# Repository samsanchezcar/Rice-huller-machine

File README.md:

<div align="center">

# DAMSPI-150
## Descascaradora de Arroz Modular Semiautomática con Pesaje Integrado

**Proyecto Aplicado de Ingeniería — 2017275 | 1er Semestre 2026**
**Universidad Nacional de Colombia · Facultad de Ingeniería · Grupo B**

</div>

---

## Tabla de Contenido

1. [Resumen Ejecutivo](#1-resumen-ejecutivo)
2. [Equipo de Trabajo](#2-equipo-de-trabajo)
3. [Estructura del Repositorio](#3-estructura-del-repositorio)
4. [Arquitectura del Sistema](#4-arquitectura-del-sistema)
5. [Guía de Fase del Proyecto](#5-guía-de-fase-del-proyecto)
6. [Proveedores Clave](#6-proveedores-clave)
7. [Instrucciones de Uso](#7-instrucciones-de-uso)
8. [Estado de Componentes](#8-estado-de-componentes)
9. [Pendientes por Fase](#9-pendientes-por-fase)
10. [Normas y Convenciones del Repositorio](#10-normas-y-convenciones-del-repositorio)

---

## 1. Resumen Ejecutivo

El **DAMSPI-150** es un equipo semiautomático para el descascarillado de arroz paddy (*Oryza sativa*) diseñado para operar en campo, sin acceso a red eléctrica, con capacidad de **150 kg/h**. Surge de la necesidad de los pequeños y medianos productores de arroz de la región de Neiva (Huila) de reducir su dependencia de los molinos industriales y aumentar el valor agregado de su producto en origen.

El sistema está organizado en **4 módulos desmontables** con peso máximo de 25 kg cada uno, permitiendo su transporte y montaje por dos o tres personas sin herramientas especializadas. Incorpora un **sistema de control automático de pesaje** que detiene el proceso al alcanzar el peso de un bulto objetivo (10, 25 o 50 kg), accionando el embrague electromagnético y la compuerta de la tolva.

| Parámetro | Valor |
|-----------|-------|
| Nombre del sistema | DAMSPI-150 |
| Solicitante | Diego Alexander Castro Neira — Diego Castro Industria y Construcción S.A.S. |
| Capacidad objetivo | 150 kg/h de arroz paddy (humedad 18–22%) |
| Motor | Gasolina 6.5 HP / 3600 RPM (ya adquirido) |
| Módulos | 4 módulos desmontables (Potencia, Descascarillado, Control/Pesaje, Chasis) |
| Peso máx. por módulo | ≤ 25 kg |
| Presupuesto total | $7.000.000 COP (aportado por solicitante) |
| Presupuesto estimado | ~$5.980.000 COP (margen de ~$1.020.000) |
| Microcontrolador | PIC18F4550 |
| Interfaz de usuario | LCD 20×4 I2C + Teclado matricial 4×4 |
| Embrague | Electromagnético DC 24V — DLD6-05 tipo A |
| Eficiencia descascarillado | ≥ 85% en primera pasada |
| Precisión pesaje | ±100 g |
| Tiempo de ensamble | ≤ 60 minutos |
| Piezas estructurales | Manufactura aditiva FDM (PETG / PLA+) con optimización topológica previa |
| Semestre | 1er Semestre 2026 (14 semanas: 3 Feb – 30 May 2026) |

---

## 2. Equipo de Trabajo

| Nombre | Código | Área Principal | Responsabilidades Clave |
|--------|--------|---------------|------------------------|
| **Nicolás Herreño Fuentes** | — | Diseño Mecánico (Líder) | Cálculos de transmisión, memorias de cálculo, CAD Onshape, planos de fabricación |
| **Sebastián D. Millan B.** | — | Diseño Mecánico | Cálculos elementos de máquinas, CAD, diseño eje secundario |
| **Andrés G. Pinilla M.** | — | Manufactura y CAD | Talleres externos, Onshape, optimización topológica + FDM |
| **Samuel D. Sánchez C.** | — | Electrónica / Control / **Gestión** | Firmware PIC18F4550, sistema de pesaje, **gestión de proveedores, cotizaciones, BOM, compras**, finanzas |
| **Gabriel E. Bojacá M.** | — | Electrónica / Financiero | Circuito electrónico, PCB, interfaz LCD-teclado, gestión presupuesto |
| **Santiago Ávila C.** | — | Eléctrico / Potencia | Alternador, carga batería, cableado potencia, sistema eléctrico Módulo 1 |

> **Nota de gestión**: Samuel es el responsable único de toda la coordinación con proveedores: contacto inicial, solicitud de cotizaciones, seguimiento de pedidos, recepción de componentes y registro en el BOM. Toda compra debe quedar registrada antes de ejecutarse.

---

## 3. Estructura del Repositorio

```
DAMSPI-150/
│
├── README.md                          ← Este archivo — guía maestra del proyecto
│
├── 01_Informe/                        ← Informes de avance (Partes I, II y III)
│   ├── Informe_Avance_Parte_I_Descascaradora.docx   ← Entrega S4 (completada)
│   ├── Informe_Parte_II_Diseño_Detallado.docx        ← Entrega S8 (en progreso)
│   ├── Informe_Parte_III_Final.docx                  ← Entrega S14 (pendiente)
│   ├── boceto_arquitectura_modular.png
│   ├── sistema_potencia_electrica.svg
│   └── Diagramas_bloques.pdf
│
├── 02_Actas/                          ← Actas semanales y documentos legales
│   ├── Acuerdo_Solicitante.pdf        ← AS firmado
│   ├── contrato_social.pdf            ← CS firmado
│   ├── Acta_S01.pdf
│   ├── Acta_S02.pdf
│   ├── Acta_S03.pdf
│   └── Acta_SColchon.pdf
│
├── 03_Cronograma_GANTT/               ← Planificación y seguimiento
│   ├── GANTT_Descascaradora_v2.xlsx   ← GANTT original (referencia)
│   └── GANTT-PAI1B.pdf
│
├── 04_BOM/                            ← Lista de materiales
│   └── BOM_Descascaradora_v1.xlsx     ← BOM con 34 ítems (~$5.98M COP)
│
├── 05_CAD_Planos/                     ← Modelos 3D y planos de fabricación
│   ├── Onshape_Link.md                ← Enlace al modelo Onshape compartido
│   └── (exportar aquí planos PDF/DWG al finalizar cada módulo)
│
├── 06_Estado_del_Arte_Referencias/    ← Literatura técnica y normativa
│   ├── Baker_Tribologia_Molineria_Arroz.pdf
│   ├── Design_Fabrication_Rice_Hulling.pdf
│   ├── Manual_Tecnico_Descascaradora_Referencia.pdf
│   ├── Referencia_Adicional_Procesamiento_Arroz.pdf
│   └── rm05.pdf
│
├── 07_Bitacoras/                      ← Bitácoras semanales individuales
│   ├── Bitacora_Nicolas.md
│   ├── Bitacora_Sebastian.md
│   ├── Bitacora_Andres.md
│   ├── Bitacora_Samuel.md
│   ├── Bitacora_Gabriel.md
│   └── Bitacora_Santiago.md
│
├── 08_Electronica/                    ← Todo lo electrónico (MCU, sensores, firmware)
│   ├── GUIA_ELECTRONICA.md            ← Guía técnica electrónica completa ★
│   ├── firmware/                      ← Código fuente PIC18F4550
│   │   ├── DAMSPI150.X/              ← Proyecto MPLAB X
│   │   └── LibLCD_I2C_XC8.h         ← Librería LCD I2C para XC8
│   └── esquematicos/                  ← Esquemáticos del circuito de control
│
├── 09_Electrica/                      ← Todo lo eléctrico (potencia, alternador, batería)
│   ├── GUIA_ELECTRICA.md             ← Guía técnica eléctrica-potencia completa ★
│   └── diagramas/                     ← Diagramas del sistema de potencia eléctrica
│
└── 10_Gestion/                        ← Gestión del proyecto
    ├── GESTION_PROYECTO.md            ← EDT detallado + Gantt + gestión compras ★
    ├── REGISTRO_PROVEEDORES.md        ← Contactos, cotizaciones y seguimiento (Samuel)
    └── CONTROL_PRESUPUESTO.md        ← Control de gastos vs. presupuesto
```

> Los archivos marcados con **★** son documentos técnicos vivos que deben actualizarse semanalmente.

---

## 4. Arquitectura del Sistema

El DAMSPI-150 se organiza en cuatro módulos funcionales independientes:

```
┌─────────────────────────────────────────────────────────────────────┐
│                    DAMSPI-150 — VISTA FUNCIONAL                     │
├──────────────┬──────────────────┬──────────────────┬───────────────┤
│  MÓDULO 1    │    MÓDULO 2      │    MÓDULO 3       │  MÓDULO 4     │
│  POTENCIA    │  DESCASCARILLADO │  CONTROL/PESAJE   │  CHASIS       │
│              │                  │                   │               │
│ Motor 6.5HP  │  Rodillos PU     │  PIC18F4550       │  Estructura   │
│ Alternador   │  Ø80mm / 200mm   │  LCD 20×4 I2C     │  acero 40×40  │
│ Batería 24V  │  Ventilador      │  Teclado 4×4      │  Chasis       │
│ Embrague     │  centrífugo      │  HX711 + 4 celdas │  soldado      │
│ Boost 14→24V │  Sin Fín alim.   │  SSR + Embrague   │  Ruedas       │
│ Buck 24→5V   │  Pulidora horiz. │  Servo tolva      │  Pasadores    │
│              │  (opcional)      │  Pilotos / Buzzer │  conex. rápida│
│  ~22 kg      │  ~18 kg          │  ~8 kg            │  ~15 kg       │
└──────────────┴──────────────────┴──────────────────┴───────────────┘
       │                │                  │                │
       └────────────────┴──────────────────┴────────────────┘
                    Correas en V / Poleas / Ejes de transmisión
```

**Documentación técnica por área:**

| Área | Documento | Responsable |
|------|-----------|-------------|
| Sistema electrónico (MCU, firmware, sensores, interfaz) | [`08_Electronica/GUIA_ELECTRONICA.md`](08_Electronica/GUIA_ELECTRONICA.md) | Samuel, Gabriel |
| Sistema eléctrico (potencia, alternador, batería, carga) | [`09_Electrica/GUIA_ELECTRICA.md`](09_Electrica/GUIA_ELECTRICA.md) | Santiago, Samuel |
| Gestión, EDT, Gantt, proveedores, compras | [`10_Gestion/GESTION_PROYECTO.md`](10_Gestion/GESTION_PROYECTO.md) | Samuel |

---

## 5. Guía de Fase del Proyecto

### Semana Actual → Ver `10_Gestion/GESTION_PROYECTO.md` para detalle completo

| Fase | Semanas | Estado | Entregable |
|------|---------|--------|------------|
| **F1** — Formulación y requisitos | S1–S3 | ✅ Completada | Informe Parte I |
| **F2** — Diseño Módulo Potencia | S3–S6 | 🔄 En progreso | Memorias cálculo + CAD |
| **F3** — Diseño Electrónico y Control | S4–S7 | 🔄 En progreso | Circuito + Firmware |
| **F4** — Diseño Módulo Descascarillado | S3–S8 | 🔄 En progreso | Informe Parte II |
| **F4G** — Gestión proveedores y compras | S3–S10 | 🔄 En progreso | Registro Proveedores |
| **F5** — Manufactura y montaje | S8–S12 | ⏳ Pendiente | Prototipo ensamblado |
| **F6** — Validación y pruebas | S12–S13 | ⏳ Pendiente | Video + resultados |
| **F7** — Documentación y entrega | S13–S14 | ⏳ Pendiente | Informe Parte III |

### Checklist de la Semana en Curso

Antes de cada reunión semanal, verificar:

- [ ] Acta de la semana anterior firmada y archivada en `02_Actas/`
- [ ] Bitácoras individuales actualizadas en `07_Bitacoras/`
- [ ] BOM actualizado con nuevas adquisiciones o cotizaciones (`04_BOM/`)
- [ ] Samuel: actualizar `10_Gestion/REGISTRO_PROVEEDORES.md` con estado de pedidos
- [ ] Avance de CAD subido a Onshape (link en `05_CAD_Planos/Onshape_Link.md`)
- [ ] Samuel/Gabriel: commits de firmware en `08_Electronica/firmware/`
- [ ] GANTT actualizado con estado real de avance

---

## 6. Proveedores Clave

| Proveedor | Productos | Contacto | Responsable |
|-----------|-----------|----------|-------------|
| **Solagro Colombia** | Rodillos PU Ø80mm, pulidora horizontal, repuestos | solagro.co/repuestos | Samuel |
| **MercadoLibre Colombia** | Embrague DLD6-05, SSR, electrónica general | mercadolibre.com.co | Samuel |
| **AliExpress** | Celdas de carga tipo S, PIC18F4550, batería LiFePO4, LCD 20×4, teclado 4×4 | aliexpress.com | Samuel |
| **Homecenter** | Motor 6.5HP (ya adquirido) | homecenter.com.co | — |
| **Ferreterías industriales Bogotá** | Perfiles acero, tornillería, rodamientos, poleas | Local Bogotá | Gabriel / Samuel |
| **Taller externo UNAL** | Mecanizado ejes, soldadura chasis | Campus UNAL | Nicolás, Andrés |
| **Naylampmechatronics** | HX711, electrónica | naylampmechatronics.com | Samuel |
| **Siesa Industrial** | E-Stop, pilotos LED industriales | Local Bogotá | Samuel |

> **Ver detalle completo de cotizaciones y contactos en:** [`10_Gestion/REGISTRO_PROVEEDORES.md`](10_Gestion/REGISTRO_PROVEEDORES.md)

---

## 7. Instrucciones de Uso

### Informe Principal
1. Abrir `01_Informe/Informe_Avance_Parte_*.docx` en Word/Google Docs
2. Actualizar tabla de contenido: **Referencias → Actualizar tabla → Todo el documento**
3. No modificar estructura de secciones sin actualizar el TOC

### BOM
- Abrir `04_BOM/BOM_Descascaradora_v1.xlsx`
- Totales calculados automáticamente (columna H = E × G)
- **Columna Estado**: `ADQUIRIDO` / `COTIZADO` / `Por adquirir` / `Por adquirir (Solagro)`
- Actualizar inmediatamente al recibir cualquier componente o cotización
- Samuel notifica al grupo cada actualización

### GANTT
- Abrir `03_Cronograma_GANTT/GANTT_Descascaradora_v2.xlsx`
- Actualizar al inicio de cada semana con estado real
- EDT completo y mejorado en `10_Gestion/GESTION_PROYECTO.md`

### Firmware (Electrónica)
- Abrir `08_Electronica/firmware/DAMSPI150.X/` con **MPLAB X IDE ≥ 6.0**
- Compilador: **XC8 ≥ 3.0**
- Programador: **PICkit 3 o PICkit 4** (ICSP)
- Ver documentación completa en `08_Electronica/GUIA_ELECTRONICA.md`

### CAD (Onshape)
- Link al modelo compartido en `05_CAD_Planos/Onshape_Link.md`
- Exportar planos PDF/DWG a `05_CAD_Planos/` al completar cada módulo
- Usar prefijo de versión: `v1.0_`, `v1.1_`, etc.

---

## 8. Estado de Componentes

| N° | Componente | Módulo | Precio Unit. | Estado | Resp. |
|----|-----------|--------|-------------|--------|-------|
| 1 | Motor gasolina 6.5HP | Mod.1 | $750.000 | ✅ ADQUIRIDO | — |
| 2 | Embrague DLD6-05 24V | Mod.1 | $300.000 | 📋 COTIZADO | Samuel |
| 3 | Celda de carga tipo S 10kg ×4 | Mod.3 | $57.045 c/u | 📋 COTIZADO | Samuel |
| 4 | PIC18F4550 DIP-40 | Mod.3 | $31.018 | 📋 COTIZADO | Samuel |
| 5 | Batería LiFePO4 24V/5Ah | Mod.1 | $250.000 | 📋 COTIZADO | Santiago |
| 6 | HX711 ADC 24 bits | Mod.3 | $15.000 | 🛒 Por adquirir | Samuel |
| 7 | LCD 20×4 + módulo I2C | Mod.3 | $25.000 | 🛒 Por adquirir | Samuel |
| 8 | Teclado matricial 4×4 | Mod.3 | $15.000 | 🛒 Por adquirir | Samuel |
| 9 | Rodillos PU Ø80mm (par) | Mod.2 | $400.000 | 🔍 Solagro | Samuel |
| 10 | Pulidora horizontal | Mod.2 | $600.000 | 🔍 Solagro | Samuel |
| 11 | Alternador motocicleta | Mod.1 | $180.000 | 🛒 Por adquirir | Santiago |
| … | *(ver BOM completo)* | — | — | — | — |

> Leyenda: ✅ Adquirido | 📋 Cotizado | 🛒 Por adquirir | 🔍 En gestión con proveedor específico

---

## 9. Pendientes por Fase

### Fase Actual (S4–S7) — Diseño Detallado

**Mecánica (Nicolás, Sebastián, Andrés):**
- [ ] Memorias de cálculo: eje secundario, transmisión por poleas
- [ ] Diseño CAD Módulo 2: rodillos, ajustador, ventilador, Sin Fín
- [ ] Diseño CAD Módulo 4: chasis, puntos de conexión rápida
- [ ] Optimización topológica de piezas para FDM (Andrés)
- [ ] Contacto con taller externo para mecanizado de ejes

**Electrónica (Samuel, Gabriel):**
- [ ] Diseño esquemático PCB del circuito de control (Módulo 3)
- [ ] Iniciar firmware: `initPorts()`, `initLCD_I2C()`, `hx711_init()`
- [ ] Selección y pedido: LCD 20×4, teclado 4×4, HX711, SSR

**Eléctrica (Santiago, Samuel):**
- [ ] Diseño detallado: alternador → rectificador → boost → batería
- [ ] Cotización del Boost DC-DC 14V→24V 5A
- [ ] Diseño de canaletas y cableado entre módulos

**Gestión (Samuel):**
- [ ] Contactar Solagro para rodillos y pulidora (cotización formal)
- [ ] Confirmar pedido AliExpress: celdas de carga, PIC, batería
- [ ] Actualizar REGISTRO_PROVEEDORES.md con tiempos de entrega

### Siguiente Entrega (Parte II — Semana 8)
- [ ] Diseño conceptual con bocetos de todos los módulos
- [ ] Diagramas de caja negra y caja gris
- [ ] Memorias de cálculo completas (transmisión, rodillos, ejes)
- [ ] Modelos CAD 3D avanzados en Onshape
- [ ] Planos preliminares de fabricación
- [ ] Cronograma definitivo actualizado

---

## 10. Normas y Convenciones del Repositorio

### Nomenclatura de Archivos
```
[Módulo]_[Descripción]_v[X.Y].[ext]
Ejemplos:
  Mod3_Esquematico_Control_v1.0.pdf
  Mod1_CAD_BaseMotor_v2.1.step
  Acta_S05_20260310.pdf
```

### Versionado de Documentos
- `v1.0` → Primera versión entregable
- `v1.X` → Correcciones menores (sin cambio de estructura)
- `v2.0` → Revisión mayor (cambio de diseño o nueva fase)

### Convenciones de Código (Firmware)
- Comentarios en español
- Funciones: `camelCase` (ej. `realizarTara()`)
- Constantes: `MAYUSCULAS_CON_GUION` (ej. `PESO_OBJETIVO_KG`)
- Un archivo por módulo funcional (ver `08_Electronica/GUIA_ELECTRONICA.md`)

### Actualización del BOM
- Toda compra, cotización o cambio de precio debe registrarse el mismo día
- Samuel envía resumen semanal al grupo por WhatsApp/Discord
- Los precios en el BOM son precios de compra real (no estimados)

---

## Información del Solicitante

| Campo | Valor |
|-------|-------|
| Nombre | Diego Alexander Castro Neira |
| Empresa | Diego Castro Industria y Construcción S.A.S. |
| NIT | 9009608102 |
| Correo | dicaindustria@gmail.com |
| Teléfono | 315-255-2560 |
| Ubicación de entrega | Neiva, Huila, Colombia |

---

*Versión: 2.0 | Última actualización: Abril 2026 | Equipo Grupo B — PAI 2017275*

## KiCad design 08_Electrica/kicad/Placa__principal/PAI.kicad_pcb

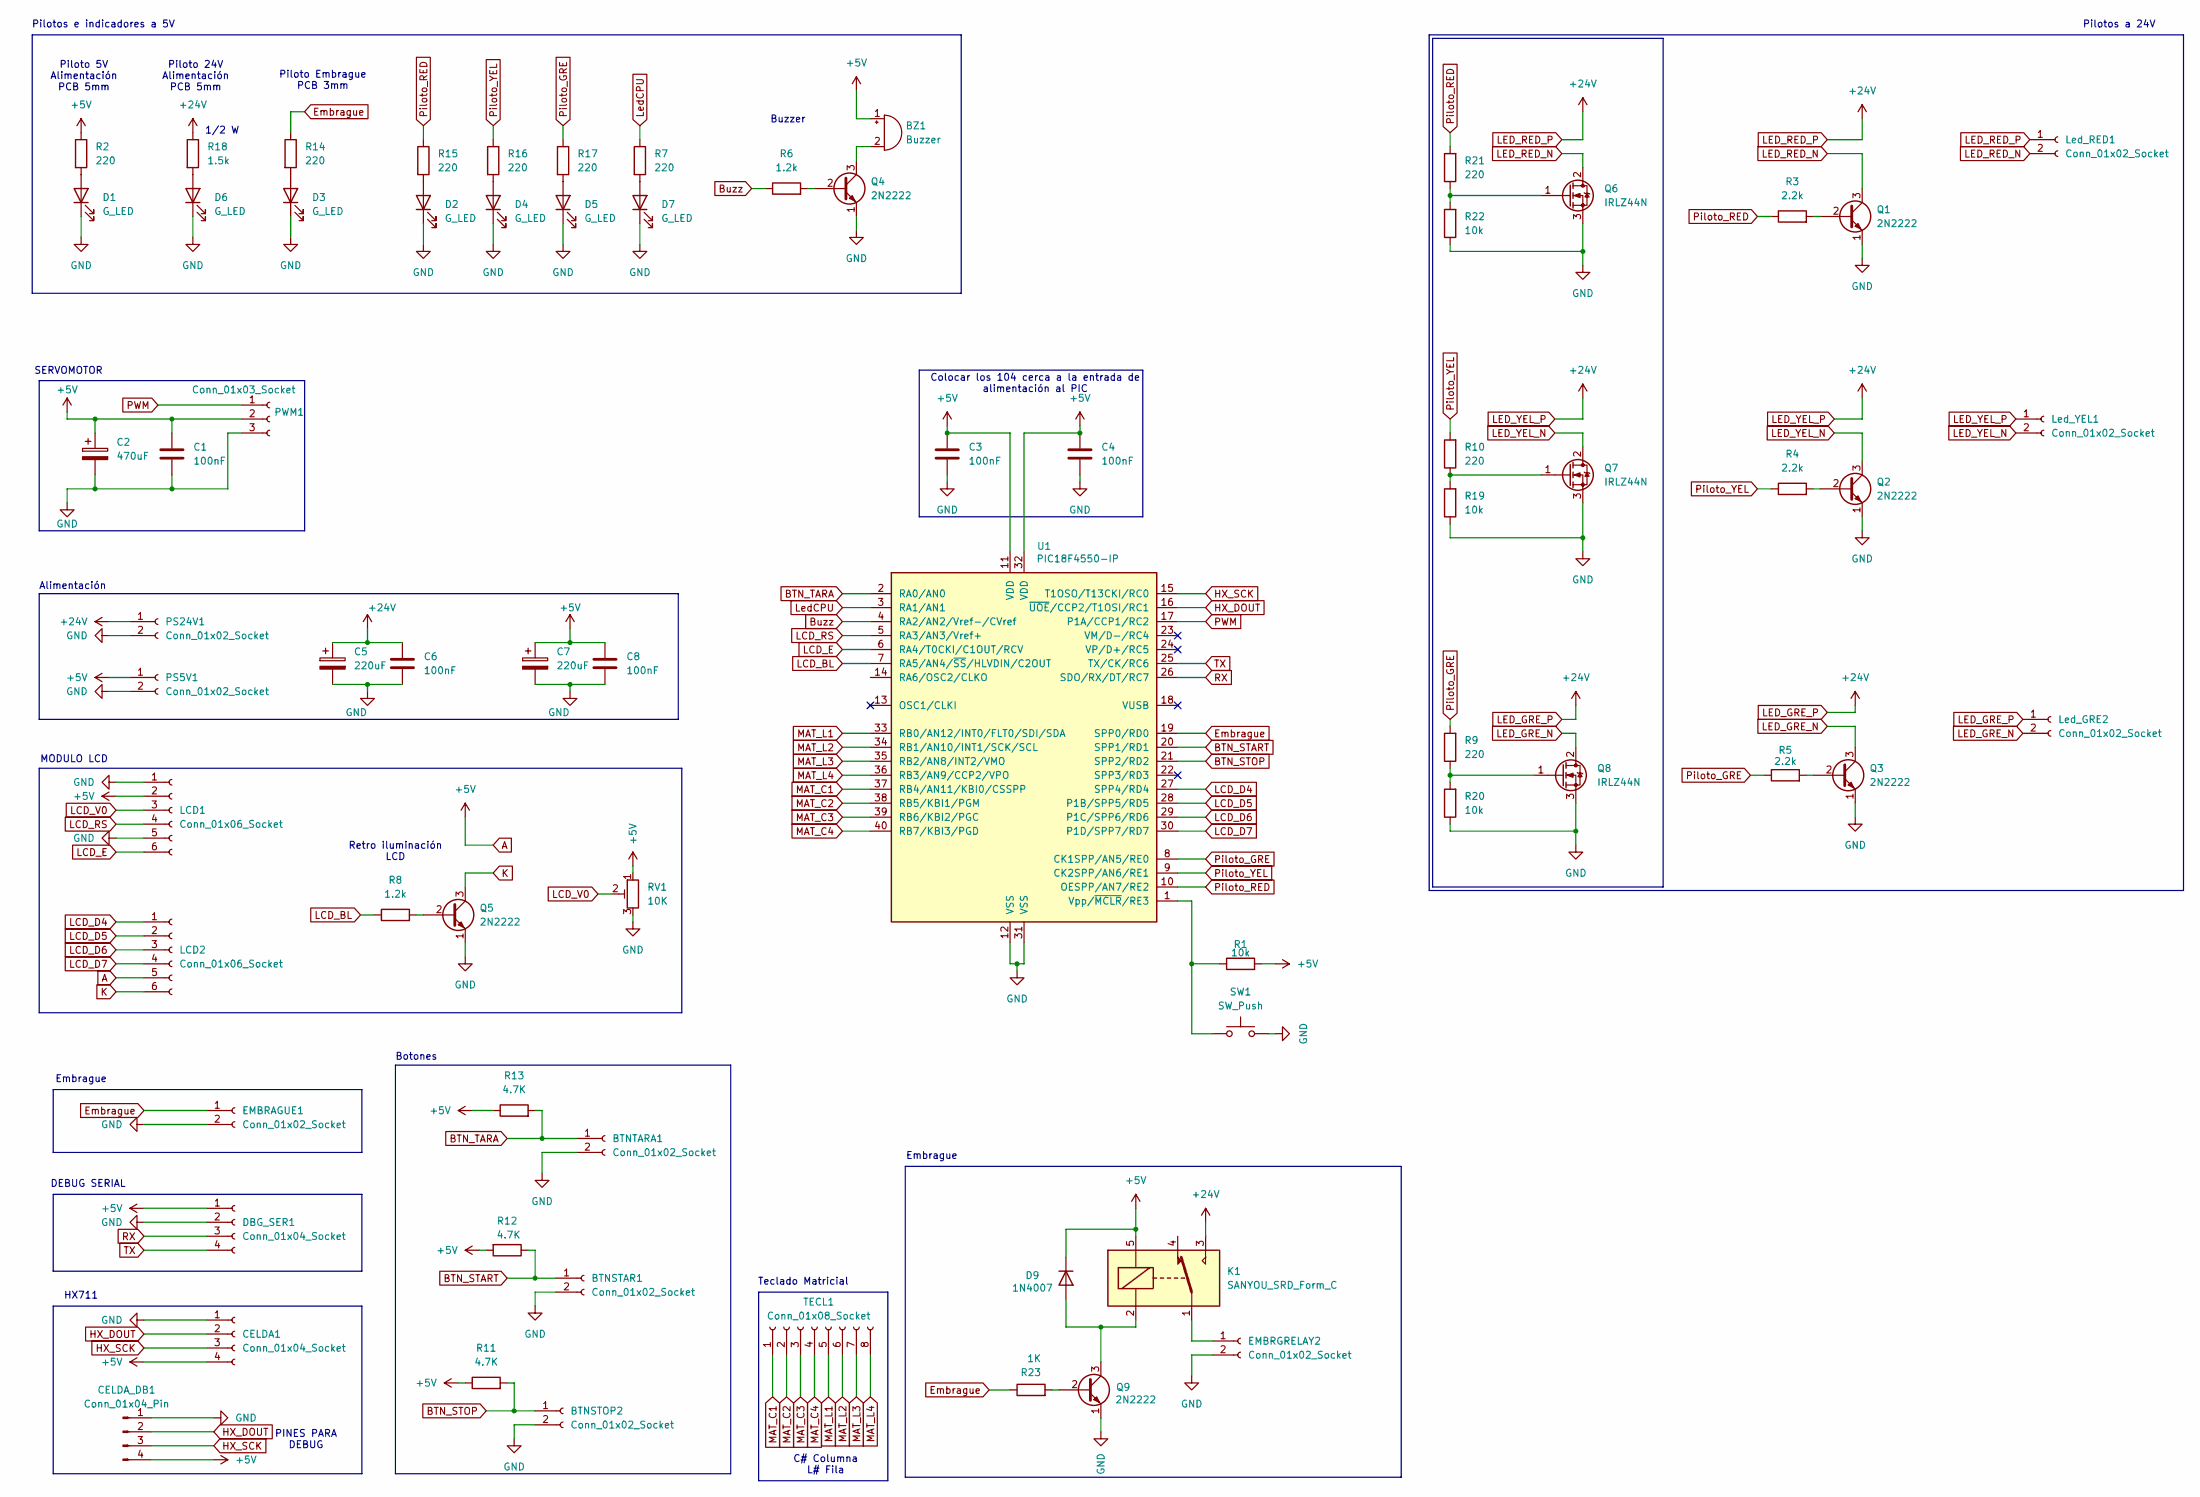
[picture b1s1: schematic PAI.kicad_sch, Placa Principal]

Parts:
BTNSTAR1: Conn_01x02_Socket; TerminalBlock_bornier-2_P5.08mm
BTNSTOP2: Conn_01x02_Socket; TerminalBlock_bornier-2_P5.08mm
BTNTARA1: Conn_01x02_Socket; TerminalBlock_bornier-2_P5.08mm
BZ1: Buzzer; Buzzer_12x9.5RM7.6
C1, C3, C4, C6, C8: 100nF; C_Disc_D6.0mm_W2.5mm_P5.00mm
C2: 470uF; CP_Radial_D10.0mm_P5.00mm
C5, C7: 220uF; CP_Radial_D10.0mm_P5.00mm
CELDA1: Conn_01x04_Socket; TerminalBlock_bornier-4_P5.08mm
CELDA_DB1: Conn_01x04_Pin; PinSocket_1x04_P2.54mm_Vertical
D1, D2, D3, D4, D5, D6, D7: G_LED; LED_D5.0mm
D9: 1N4007; D_DO-41_SOD81_P10.16mm_Horizontal
DBG_SER1: Conn_01x04_Socket; PinHeader_1x04_P2.54mm_Vertical
EMBRAGUE1: Conn_01x02_Socket; PinHeader_1x02_P2.54mm_Vertical
EMBRGRELAY2: Conn_01x02_Socket; TerminalBlock_bornier-2_P5.08mm
K1: SANYOU_SRD_Form_C; Relay_SPDT_SANYOU_SRD_Series_Form_C
LCD1, LCD2: Conn_01x06_Socket; PinHeader_1x06_P2.54mm_Vertical
Led_GRE2: Conn_01x02_Socket; TerminalBlock_bornier-2_P5.08mm
Led_RED1: Conn_01x02_Socket; TerminalBlock_bornier-2_P5.08mm
Led_YEL1: Conn_01x02_Socket; TerminalBlock_bornier-2_P5.08mm
PS5V1, PS24V1: Conn_01x02_Socket; TerminalBlock_bornier-2_P5.08mm
PWM1: Conn_01x03_Socket; TerminalBlock_bornier-3_P5.08mm
Q1, Q2, Q3, Q4, Q5, Q9: 2N2222; TO-92L_Wide
Q6, Q7, Q8: IRLZ44N; TO-220-3_Vertical
R1, R19, R20, R22: 10k; R_Axial_DIN0207_L6.3mm_D2.5mm_P10.16mm_Horizontal
R2, R7, R9, R10, R14, R15, R16, R17, R21: 220; R_Axial_DIN0207_L6.3mm_D2.5mm_P10.16mm_Horizontal
R3, R4, R5: 2.2k; R_Axial_DIN0207_L6.3mm_D2.5mm_P10.16mm_Horizontal
R6: 1.2k; R_Axial_DIN0207_L6.3mm_D2.5mm_P10.16mm_Horizontal
R8: 1.2k; R_Axial_DIN0207_L6.3mm_D2.5mm_P15.24mm_Horizontal
R11, R12: 4.7K; R_Axial_DIN0207_L6.3mm_D2.5mm_P10.16mm_Horizontal
R13: 4.7K; R_Axial_DIN0207_L6.3mm_D2.5mm_P15.24mm_Horizontal
R18: 1.5k; R_Axial_DIN0411_L9.9mm_D3.6mm_P15.24mm_Horizontal
R23: 1K; R_Axial_DIN0207_L6.3mm_D2.5mm_P10.16mm_Horizontal
RV1: 10K; Potentiometer_Runtron_RM-065_Vertical
SW1: SW_Push; SW_PUSH_6mm
TECL1: Conn_01x08_Socket; PinHeader_1x08_P2.54mm_Vertical
U1: PIC18F4550-IP; DIP-40_W15.24mm_Socket

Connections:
A: BZ1.1 (+), C1.1, C2.1, C3.1, C4.1, C7.1, C8.1, CELDA1.4, CELDA_DB1.4, D9.1 (K), DBG_SER1.1, K1.5, LCD1.2, LCD2.5, PS5V1.1, PWM1.2, R1.2, R2.1, R11.1, R12.2, R13.1, RV1.1, U1.11 (VDD), U1.32 (VDD)
BTN_START: BTNSTAR1.1, R12.1, U1.20 (SPP1/RD1)
BTN_STOP: BTNSTOP2.1, R11.2, U1.21 (SPP2/RD2)
BTN_TARA: BTNTARA1.1, R13.2, U1.2 (RA0/AN0)
Buzz: R6.1, U1.4 (RA2/AN2/Vref-/CVref)
Embrague: EMBRAGUE1.1, R14.1, R23.1, U1.19 (SPP0/RD0)
GND: BTNSTAR1.2, BTNSTOP2.2, BTNTARA1.2, C1.2, C2.2, C3.2, C4.2, C5.2, C6.2, C7.2, C8.2, CELDA1.1, CELDA_DB1.1, D1.1 (K), D2.1 (K), D3.1 (K), D4.1 (K), D5.1 (K), D6.1 (K), D7.1 (K), DBG_SER1.2, EMBRAGUE1.2, EMBRGRELAY2.2, LCD1.1, LCD1.5, PS5V1.2, PS24V1.2, PWM1.3, Q1.1 (E), Q2.1 (E), Q3.1 (E), Q4.1 (E), Q5.1 (E), Q6.3 (S), Q7.3 (S), Q8.3 (S), Q9.1 (E), R19.1, R20.1, R22.1, RV1.3, SW1.2, U1.12 (VSS), U1.31 (VSS)
HX_DOUT: CELDA1.2, CELDA_DB1.2, U1.16 (~UOE/CCP2/T1OSI/RC1)
HX_SCK: CELDA1.3, CELDA_DB1.3, U1.15 (T1OSO/T13CKI/RC0)
K: LCD2.6, Q5.3 (C)
LCD_BL: R8.1, U1.7 (RA5/AN4/~SS/HLVDIN/C2OUT)
LCD_D4: LCD2.1, U1.27 (SPP4/RD4)
LCD_D5: LCD2.2, U1.28 (P1B/SPP5/RD5)
LCD_D6: LCD2.3, U1.29 (P1C/SPP6/RD6)
LCD_D7: LCD2.4, U1.30 (P1D/SPP7/RD7)
LCD_E: LCD1.6, U1.6 (RA4/T0CKI/C1OUT/RCV)
LCD_RS: LCD1.4, U1.5 (RA3/AN3/Vref+)
LCD_V0: LCD1.3, RV1.2
LED_GRE_N: Led_GRE2.2, Q3.3 (C), Q8.2 (D)
LED_GRE_P: C5.1, C6.1, K1.3, Led_GRE2.1, Led_RED1.1, Led_YEL1.1, PS24V1.1, R18.1
LED_RED_N: Led_RED1.2, Q1.3 (C), Q6.2 (D)
LED_YEL_N: Led_YEL1.2, Q2.3 (C), Q7.2 (D)
LedCPU: R7.1, U1.3 (RA1/AN1)
MAT_C1: TECL1.1, U1.37 (RB4/AN11/KBI0/CSSPP)
MAT_C2: TECL1.2, U1.38 (RB5/KBI1/PGM)
MAT_C3: TECL1.3, U1.39 (RB6/KBI2/PGC)
MAT_C4: TECL1.4, U1.40 (RB7/KBI3/PGD)
MAT_L1: TECL1.5, U1.33 (RB0/AN12/INT0/FLT0/SDI/SDA)
MAT_L2: TECL1.6, U1.34 (RB1/AN10/INT1/SCK/SCL)
MAT_L3: TECL1.7, U1.35 (RB2/AN8/INT2/VMO)
MAT_L4: TECL1.8, U1.36 (RB3/AN9/CCP2/VPO)
unnamed: BZ1.2 (-), Q4.3 (C)
unnamed: D1.2 (A), R2.2
unnamed: D2.2 (A), R15.2
unnamed: D3.2 (A), R14.2
unnamed: D4.2 (A), R16.2
unnamed: D5.2 (A), R17.2
unnamed: D6.2 (A), R18.2
unnamed: D7.2 (A), R7.2
unnamed: D9.2 (A), K1.2, Q9.3 (C)
unnamed: EMBRGRELAY2.1, K1.1
unnamed: Q1.2 (B), R3.2
unnamed: Q2.2 (B), R4.2
unnamed: Q3.2 (B), R5.2
unnamed: Q4.2 (B), R6.2
unnamed: Q5.2 (B), R8.2
unnamed: Q6.1 (G), R21.1, R22.2
unnamed: Q7.1 (G), R10.1, R19.2
unnamed: Q8.1 (G), R9.1, R20.2
unnamed: Q9.2 (B), R23.2
unnamed: R1.1, SW1.1, U1.1 (Vpp/~MCLR/RE3)
PWM: PWM1.1, U1.17 (P1A/CCP1/RC2)
Piloto_GRE: R5.1, R9.2, R17.1, U1.8 (CK1SPP/AN5/RE0)
Piloto_RED: R3.1, R15.1, R21.2, U1.10 (OESPP/AN7/RE2)
Piloto_YEL: R4.1, R10.2, R16.1, U1.9 (CK2SPP/AN6/RE1)
RX: DBG_SER1.3, U1.26 (SDO/RX/DT/RC7)
TX: DBG_SER1.4, U1.25 (TX/CK/RC6)

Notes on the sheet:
Buzzer
Pilotos a 24V
HX711
Piloto 5V Alimentación PCB 5mm
Pilotos e indicadores a 5V
Embrague
Alimentación
PINES PARA DEBUG
C# Columna L# Fila
Retro iluminación LCD
Botones
Piloto Embrague PCB 3mm
MODULO LCD
DEBUG SERIAL
SERVOMOTOR
Piloto 24V Alimentación PCB 5mm
Teclado Matricial
Colocar los 104 cerca a la entrada de alimentación al PIC
1/2 W

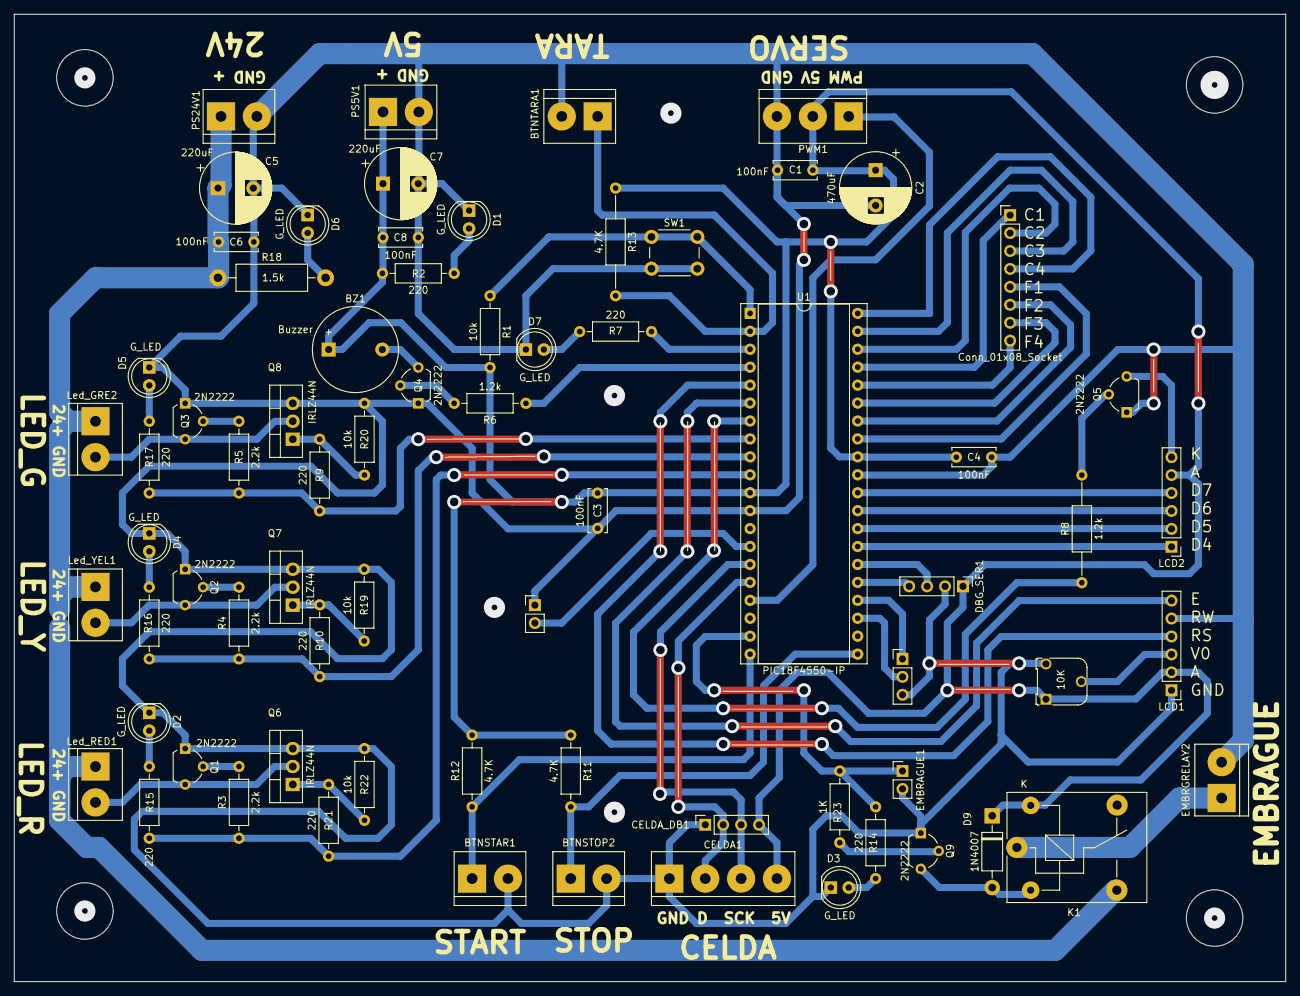
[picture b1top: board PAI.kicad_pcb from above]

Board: 2 copper layers, 180.1 x 137.0 mm, 70 parts (0 on the bottom side), 57 nets.

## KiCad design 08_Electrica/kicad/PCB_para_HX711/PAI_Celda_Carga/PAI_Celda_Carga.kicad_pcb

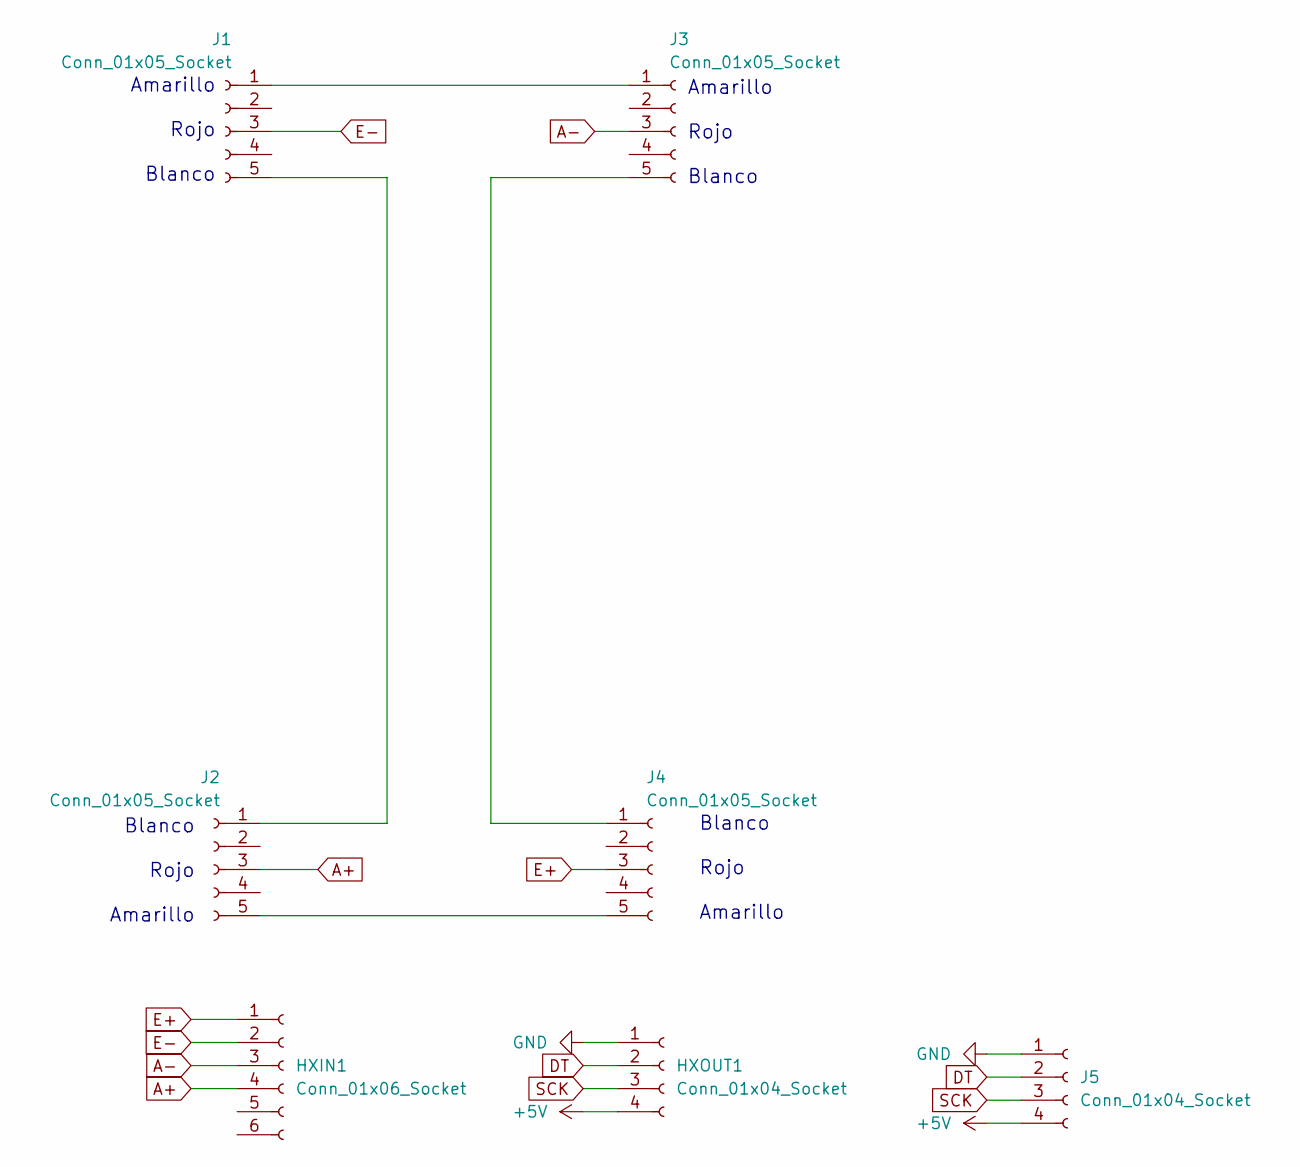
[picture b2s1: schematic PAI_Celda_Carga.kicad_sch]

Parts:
HXIN1: Conn_01x06_Socket; PinSocket_1x06_P2.54mm_Vertical
HXOUT1: Conn_01x04_Socket; PinSocket_1x04_P2.54mm_Vertical
J1, J2, J3, J4: Conn_01x05_Socket; PinSocket_1x05_P2.54mm_Vertical
J5: Conn_01x04_Socket; TerminalBlock_bornier-4_P5.08mm

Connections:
+5V: HXOUT1.4, J5.4
A+: HXIN1.4, J2.3
A-: HXIN1.3, J3.3
DT: HXOUT1.2, J5.2
E+: HXIN1.1, J4.3
E-: HXIN1.2, J1.3
GND: HXOUT1.1, J5.1
unnamed: J1.1, J3.1
unnamed: J1.5, J2.1
unnamed: J2.5, J4.5
unnamed: J3.5, J4.1
SCK: HXOUT1.3, J5.3

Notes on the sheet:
Amarillo Rojo Blanco
Blanco Rojo Amarillo
Blanco Rojo Amarillo

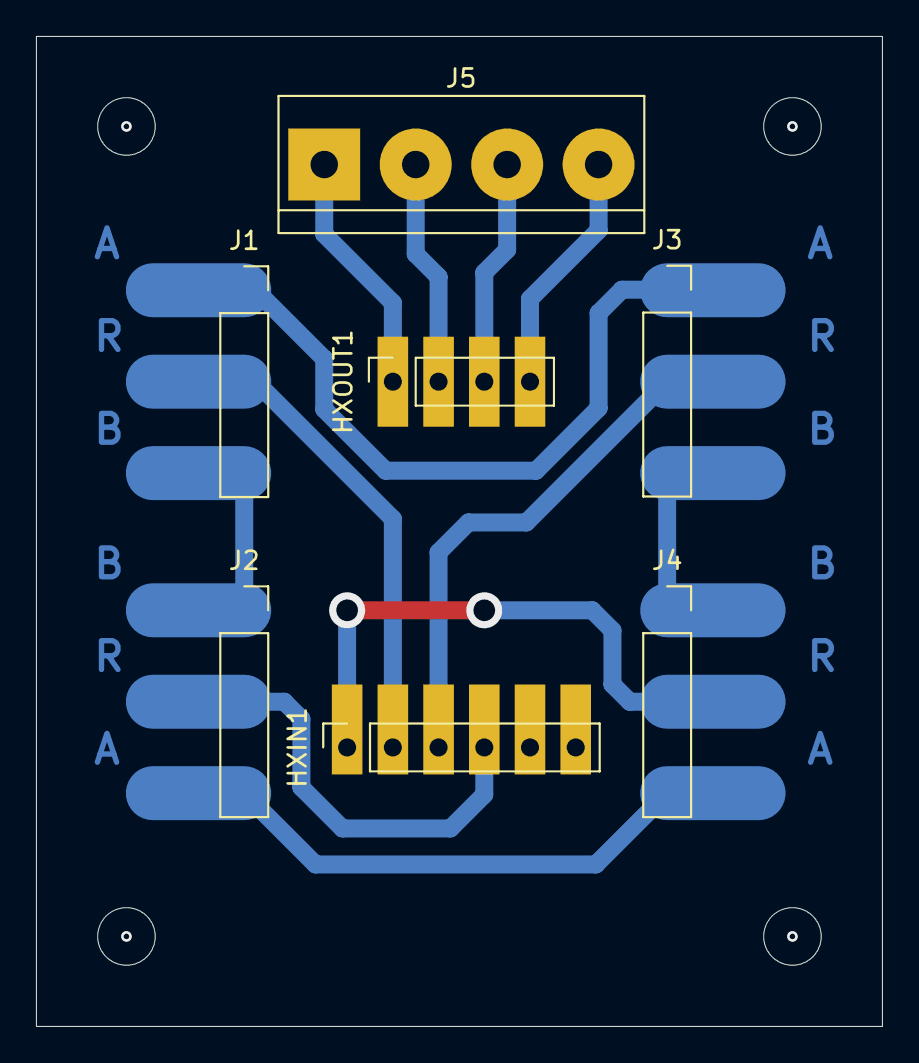
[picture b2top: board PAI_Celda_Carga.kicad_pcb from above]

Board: 2 copper layers, 47.0 x 55.0 mm, 7 parts (0 on the bottom side), 12 nets.

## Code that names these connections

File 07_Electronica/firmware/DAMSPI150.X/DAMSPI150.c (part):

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// ============================================================
// PINES
// ============================================================
#define HX_SCK      RD0             // HX711 clock (salida)
#define HX_DOUT     RD1             // HX711 data  (entrada)
#define SSR_PIN     RD3             // SSR embrague (salida)
#define BUZZER_PIN  RD4             // Buzzer activo 5V
#define LED_VERDE   RD5             // Piloto LED verde (via 2N2222)
#define LED_AMARILLO RD6            // Piloto LED amarillo
#define LED_ROJO    RD7             // Piloto LED rojo
#define ESTOP_PIN   RA4             // E-Stop NC (LOW = presionado)
#define START_PIN   RA5             // Boton START (LOW = presionado)
#define STOP_PIN    RE0             // Boton STOP  (LOW = presionado)

// Configuracion servo CCP1 (RC2) — 50 Hz @ 8 MHz, prescaler 1:16, PR2=249
#define SERVO_CERRADO   25          // 1.0 ms → 0°
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    SSPSTAT = 0b10000000;   // Slew rate control desactivado

    // Estado inicial actuadores
    SSR_PIN      = 0;       // Embrague desacoplado
    BUZZER_PIN   = 0;
    LED_VERDE    = 0;
    LED_AMARILLO = 0;
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
    // Leer 24 bits MSB primero
    for (uint8_t i = 0; i < 24; i++) {
        HX_SCK = 1;
        __delay_us(1);
        raw = (raw << 1) | (HX_DOUT ? 1 : 0);
        HX_SCK = 0;
        __delay_us(1);
    }

    // Pulso 25: selecciona ganancia 128x (canal A) para la proxima lectura
    HX_SCK = 1;
    __delay_us(1);
    HX_SCK = 0;
    __delay_us(1);

    GIE = 1;
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
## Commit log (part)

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2026-05-02 [Init] Repo Structure + Base for each area
